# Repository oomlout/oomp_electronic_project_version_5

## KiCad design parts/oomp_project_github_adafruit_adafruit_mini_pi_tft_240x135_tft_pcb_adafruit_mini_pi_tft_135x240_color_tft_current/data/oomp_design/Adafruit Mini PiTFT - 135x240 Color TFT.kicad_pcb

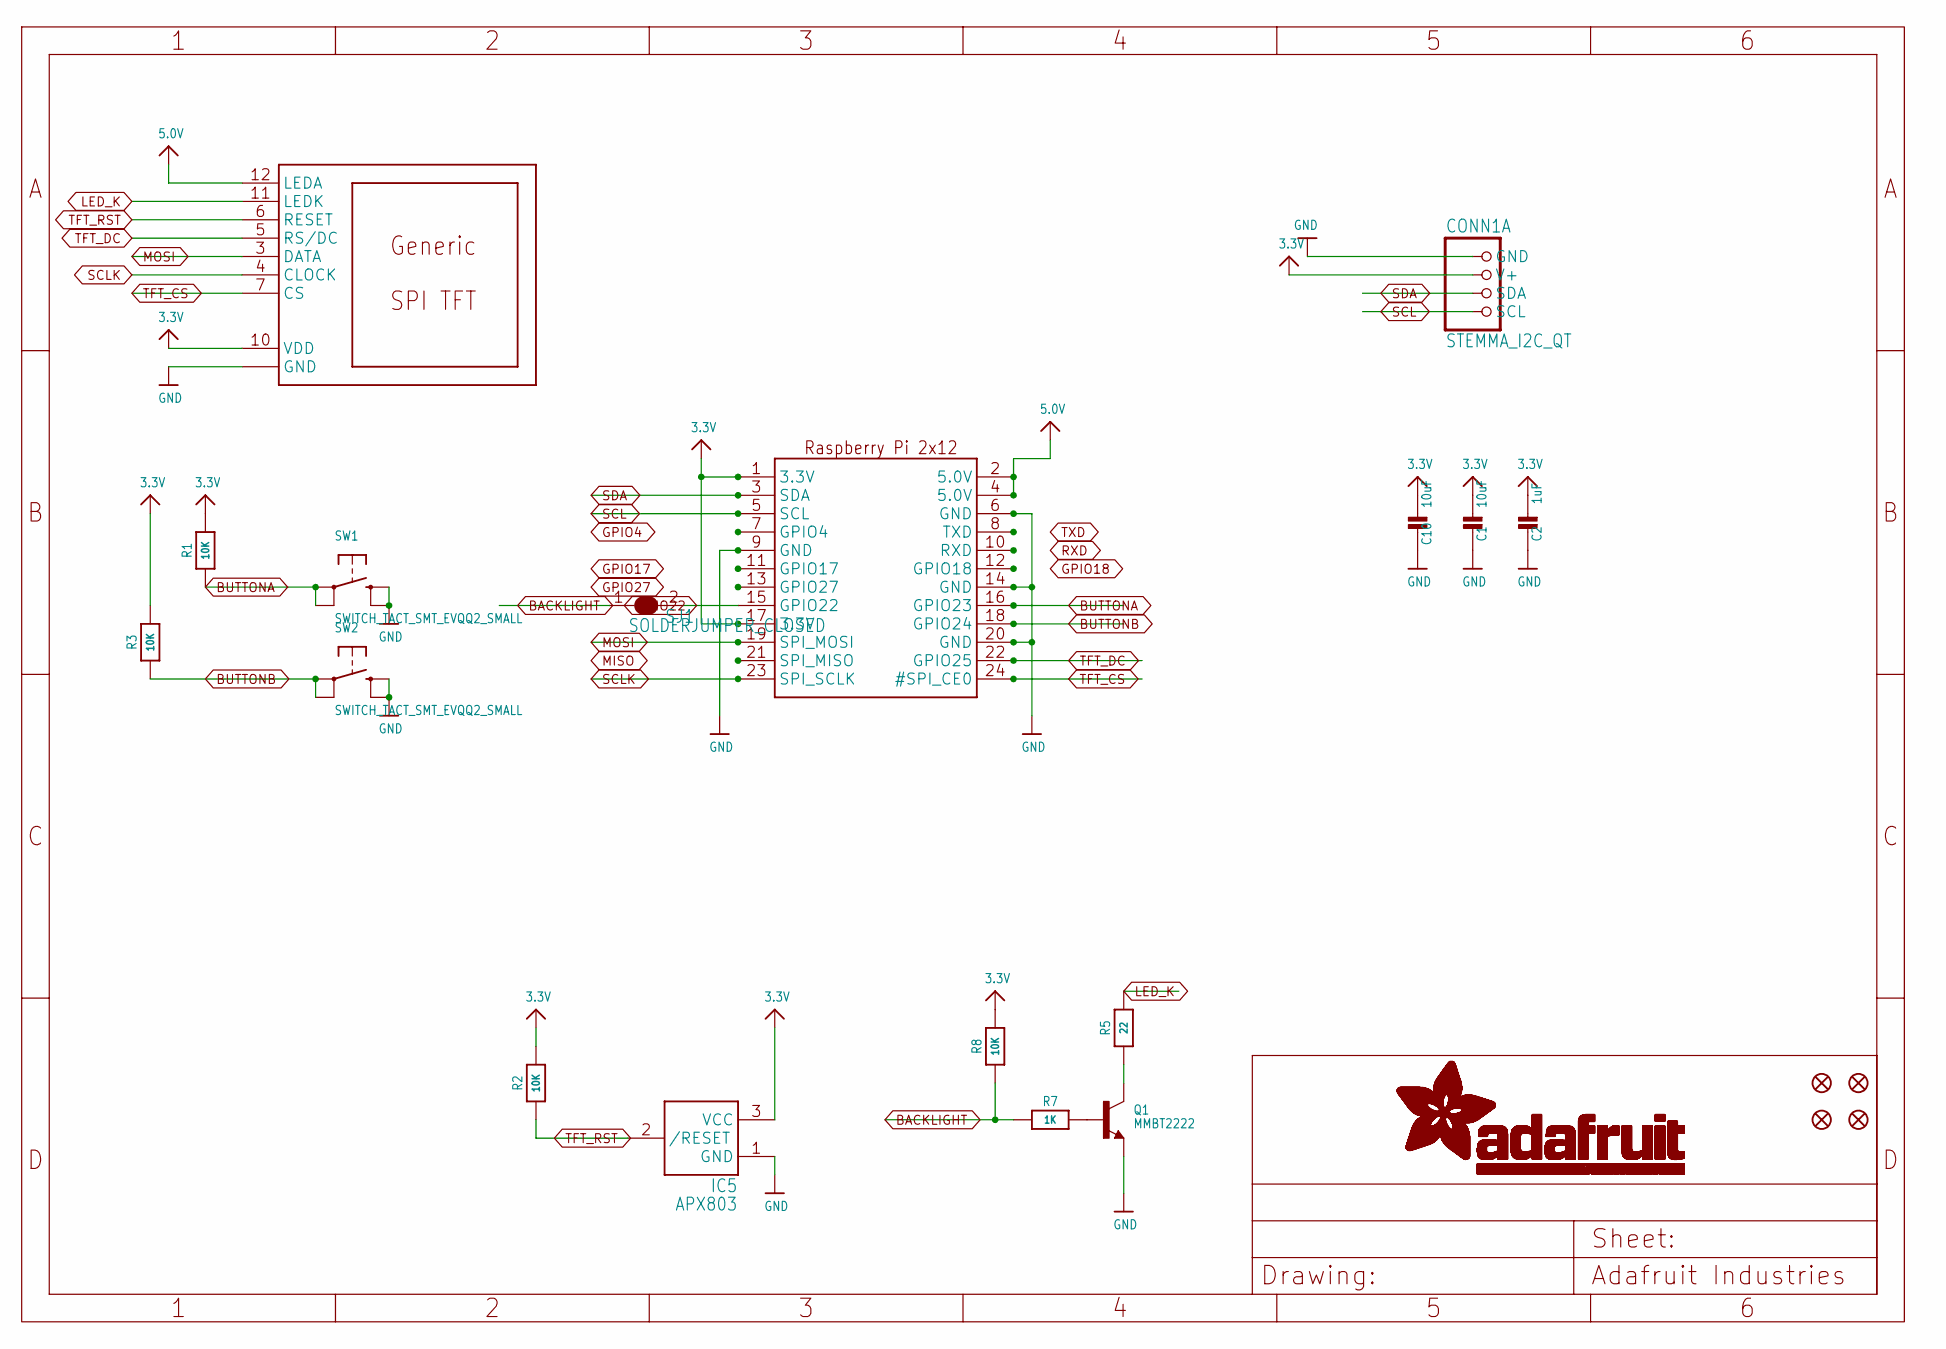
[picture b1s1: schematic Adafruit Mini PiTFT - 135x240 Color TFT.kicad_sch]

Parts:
C1, C10: 10uF; 0805-NO
C2: 1uF; 0603-NO
CONN1: STEMMA_I2C_QT; JST_SH4
DISP1: DISP_LCD_GENERIC_SPI_1.14IN_13P; TFT_1.14IN_240X135_WRAPAROUND
FID1, FID2, FID3, FID4: FIDUCIAL_1MM
IC5: APX803; SOT23
Q1: MMBT2222; SOT23-WIDE
R1, R2, R3, R8: 10K; 0603-NO
R5: 22; 0603-NO
R7: 1K; 0603-NO
RASPI1: RASPBERRYPI_2X12_THMSMT
SJ1: SOLDERJUMPER_CLOSED; SOLDERJUMPER_CLOSEDWIRE
SW1, SW2: SWITCH_TACT_SMT_EVQQ2_SMALL; EVQ-Q2_SMALLER

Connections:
3.3V: C1.2, C2.2, C10.2, CONN1.2 (V+), DISP1.10 (VDD), IC5.3 (VCC), R1.2, R2.2, R3.2, R8.2, RASPI1.1 (3.3V), RASPI1.17 (3.3V)
5.0V: DISP1.12 (LEDA), RASPI1.2 (5.0V), RASPI1.4 (5.0V)
BACKLIGHT: R7.1, R8.1, SJ1.1
BUTTONA: R1.1, RASPI1.16 (GPIO23), SW1.A, SW1.A' (P1)
BUTTONB: R3.1, RASPI1.18 (GPIO24), SW2.A, SW2.A' (P1)
GND: C1.1, C2.1, C10.1, CONN1.1 (GND), DISP1.8 (GND), DISP1.13 (GND), IC5.1 (GND), Q1.2 (E), RASPI1.6 (GND), RASPI1.9 (GND), RASPI1.14 (GND), RASPI1.20 (GND), SW1.B (S), SW1.B' (S1), SW2.B (S), SW2.B' (S1)
GPIO4: RASPI1.7 (GPIO4)
GPIO17: RASPI1.11 (GPIO17)
GPIO18: RASPI1.12 (GPIO18)
GPIO22: RASPI1.15 (GPIO22), SJ1.2
GPIO27: RASPI1.13 (GPIO27)
LED_K: DISP1.11 (LEDK), R5.2
MISO: RASPI1.21 (SPI_MISO)
MOSI: DISP1.3 (DATA), RASPI1.19 (SPI_MOSI)
unnamed: Q1.1 (B), R7.2
unnamed: Q1.3 (C), R5.1
RXD: RASPI1.10 (RXD)
SCL: CONN1.4 (SCL), RASPI1.5 (SCL)
SCLK: DISP1.4 (CLOCK), RASPI1.23 (SPI_SCLK)
SDA: CONN1.3 (SDA), RASPI1.3 (SDA)
TFT_CS: DISP1.7 (CS), RASPI1.24 (#SPI_CE0)
TFT_DC: DISP1.5 (RS/DC), RASPI1.22 (GPIO25)
TFT_RST: DISP1.6 (RESET), IC5.2 (/RESET), R2.1
TXD: RASPI1.8 (TXD)

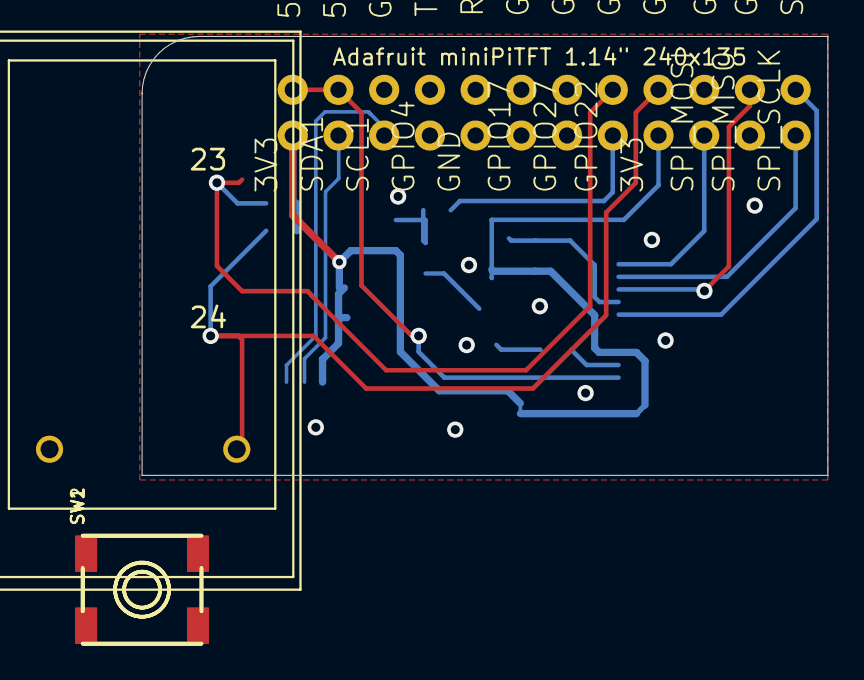
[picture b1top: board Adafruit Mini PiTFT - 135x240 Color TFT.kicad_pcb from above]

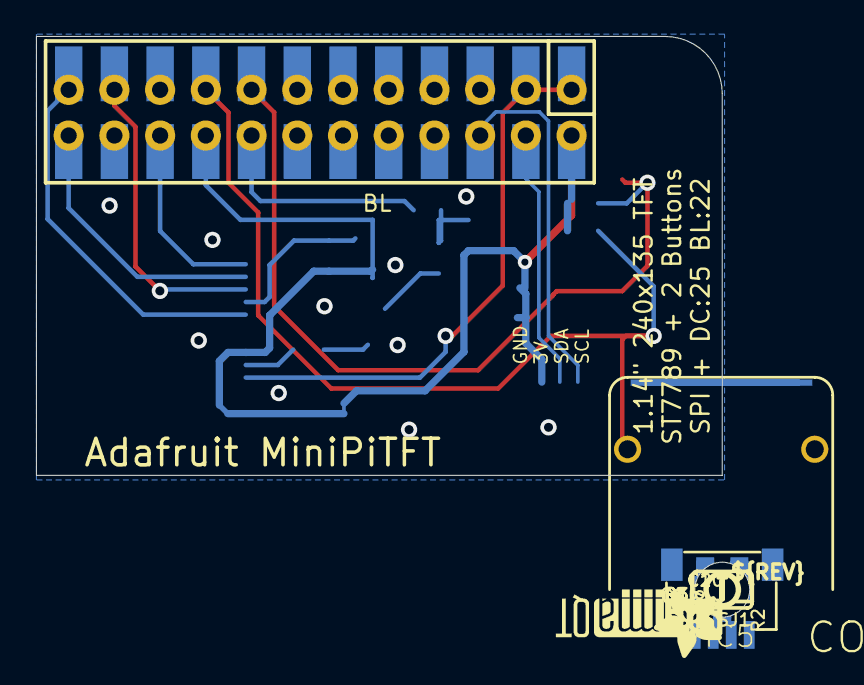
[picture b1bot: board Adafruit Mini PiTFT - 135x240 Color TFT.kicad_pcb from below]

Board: 2 copper layers, 38.1 x 24.4 mm, 25 parts (18 on the bottom side), 17 nets.

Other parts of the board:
U$4: MICROSD; ADAFRUIT_3.5MM
U$6: PCBFEAT-REV-040
U$15: STEMMAQT
UNK_HOLE_0: dummyfp0

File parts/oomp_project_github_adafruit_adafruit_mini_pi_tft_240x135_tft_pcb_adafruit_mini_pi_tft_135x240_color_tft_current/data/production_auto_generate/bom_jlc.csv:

Comment,Designator,Footprint,LCSC Part #
,"SW1,SW2",Adafruit Mini PiTFT - 135x240 Color TFT-import-fps:EVQ-Q2_SMALLER,
,U$6,Adafruit Mini PiTFT - 135x240 Color TFT-import-fps:PCBFEAT-REV-040,
,U$15,Adafruit Mini PiTFT - 135x240 Color TFT-import-fps:STEMMAQT,
10K,"R1,R2,R3,R8",Adafruit Mini PiTFT - 135x240 Color TFT-import-fps:0603-NO,C98220
10uF,"C1,C10",Adafruit Mini PiTFT - 135x240 Color TFT-import-fps:0805-NO,
1K,R7,Adafruit Mini PiTFT - 135x240 Color TFT-import-fps:0603-NO,C2907002
1uF,C2,Adafruit Mini PiTFT - 135x240 Color TFT-import-fps:0603-NO,C5673
22,R5,Adafruit Mini PiTFT - 135x240 Color TFT-import-fps:0603-NO,C23345
APX803,IC5,Adafruit Mini PiTFT - 135x240 Color TFT-import-fps:SOT23,
DISP_LCD_GENERIC_SPI_1.14IN_13P,DISP1,Adafruit Mini PiTFT - 135x240 Color TFT-import-fps:TFT_1.14IN_240X135_WRAPAROUND,
MICROSD,U$4,Adafruit Mini PiTFT - 135x240 Color TFT-import-fps:ADAFRUIT_3.5MM,
MMBT2222,Q1,Adafruit Mini PiTFT - 135x240 Color TFT-import-fps:SOT23-WIDE,
RASPBERRYPI_2X12_THMSMT,RASPI1,Adafruit Mini PiTFT - 135x240 Color TFT-import-fps:RASPBERRYPI_2X12_THMSMT,
STEMMA_I2C_QT,CONN1,Adafruit Mini PiTFT - 135x240 Color TFT-import-fps:JST_SH4,C160404

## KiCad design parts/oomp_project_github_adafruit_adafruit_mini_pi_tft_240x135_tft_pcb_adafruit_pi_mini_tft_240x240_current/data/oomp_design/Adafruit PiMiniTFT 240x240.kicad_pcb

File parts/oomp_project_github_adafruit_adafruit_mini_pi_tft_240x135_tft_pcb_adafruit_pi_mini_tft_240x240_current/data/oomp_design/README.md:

# OOMP KiCad design copy

Open `Adafruit PiMiniTFT 240x240.kicad_pro` (or the `.kicad_pcb` / `.kicad_sch`) in KiCad. Local OOMP libraries are under `libraries/`. Original inputs are preserved in [../original/](../original/).

Only verified unchanged installed KiCad defaults were renamed. Modified, custom, unmatched and unavailable items remain unchanged. Soldering variants are never swapped during conversion. Existing pad coordinates, nets and UUIDs are preserved.

See [conversion_report.yaml](conversion_report.yaml) for every conversion and skip. Copy this directory before editing; regeneration refuses to overwrite edited design files.

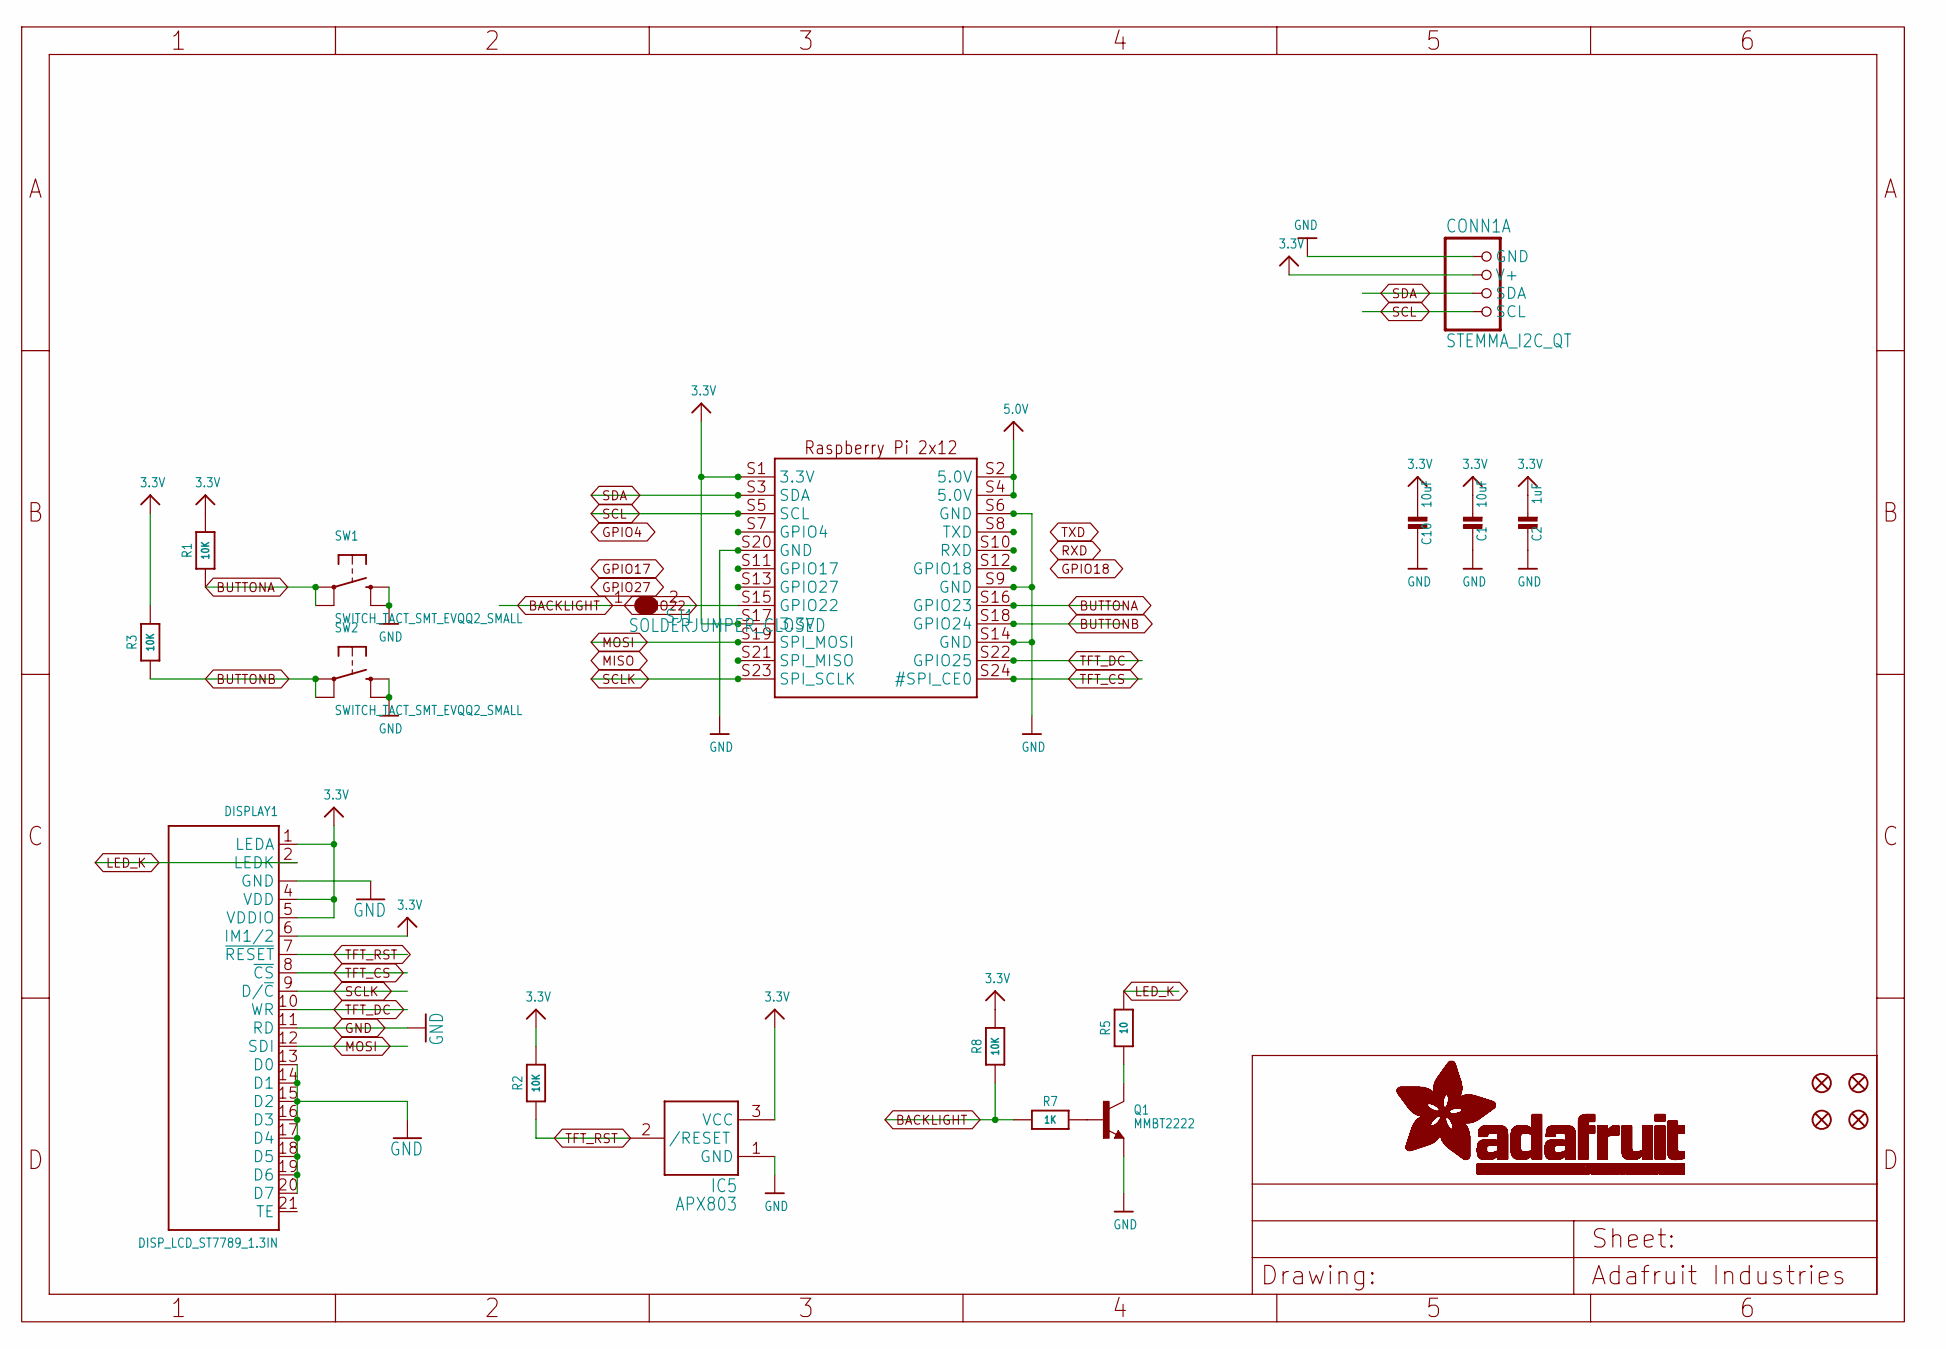
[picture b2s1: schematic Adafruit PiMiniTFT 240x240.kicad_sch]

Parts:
C1, C10: 10uF; 0805-NO
C2: 1uF; 0603-NO
CONN1: STEMMA_I2C_QT; JST_SH4
DISPLAY1: DISP_LCD_ST7789_1.3IN; TFT_1.3IN_240X240_24P
FID1, FID2, FID3, FID4: FIDUCIAL_1MM
IC5: APX803; SOT23
Q1: MMBT2222; SOT23-WIDE
R1, R2, R3, R8: 10K; 0603-NO
R5: 10; 0603-NO
R7: 1K; 0603-NO
RASPI1: RASPBERRYPI_2X12_SMT
SJ1: SOLDERJUMPER_CLOSED; SOLDERJUMPER_CLOSEDWIRE
SW1, SW2: SWITCH_TACT_SMT_EVQQ2_SMALL; EVQ-Q2_SMALLER

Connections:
3.3V: C1.2, C2.2, C10.2, CONN1.2 (V+), DISPLAY1.1 (LEDA), DISPLAY1.4 (VDD), DISPLAY1.5 (VDDIO), DISPLAY1.6 (IM1/2), IC5.3 (VCC), R1.2, R2.2, R3.2, R8.2, RASPI1.S1 (3.3V), RASPI1.S17 (3.3V)
5.0V: RASPI1.S2 (5.0V), RASPI1.S4 (5.0V)
BACKLIGHT: R7.1, R8.1, SJ1.1
BUTTONA: R1.1, RASPI1.S16 (GPIO23), SW1.A, SW1.A' (P1)
BUTTONB: R3.1, RASPI1.S18 (GPIO24), SW2.A, SW2.A' (P1)
GND: C1.1, C2.1, C10.1, CONN1.1 (GND), DISPLAY1.3 (GND), DISPLAY1.11 (RD), DISPLAY1.13 (D0), DISPLAY1.14 (D1), DISPLAY1.15 (D2), DISPLAY1.16 (D3), DISPLAY1.17 (D4), DISPLAY1.18 (D5), DISPLAY1.19 (D6), DISPLAY1.20 (D7), DISPLAY1.23 (GND), DISPLAY1.24 (GND), IC5.1 (GND), Q1.2 (E), RASPI1.S6 (GND), RASPI1.S9 (GND), RASPI1.S14 (GND), RASPI1.S20 (GND), SW1.B (S), SW1.B' (S1), SW2.B (S), SW2.B' (S1)
GPIO4: RASPI1.S7 (GPIO4)
GPIO17: RASPI1.S11 (GPIO17)
GPIO18: RASPI1.S12 (GPIO18)
GPIO22: RASPI1.S15 (GPIO22), SJ1.2
GPIO27: RASPI1.S13 (GPIO27)
LED_K: DISPLAY1.2 (LEDK), R5.2
MISO: RASPI1.S21 (SPI_MISO)
MOSI: DISPLAY1.12 (SDI), RASPI1.S19 (SPI_MOSI)
unnamed: Q1.1 (B), R7.2
unnamed: Q1.3 (C), R5.1
RXD: RASPI1.S10 (RXD)
SCL: CONN1.4 (SCL), RASPI1.S5 (SCL)
SCLK: DISPLAY1.9 (D/~C), RASPI1.S23 (SPI_SCLK)
SDA: CONN1.3 (SDA), RASPI1.S3 (SDA)
TFT_CS: DISPLAY1.8 (~CS), RASPI1.S24 (#SPI_CE0)
TFT_DC: DISPLAY1.10 (WR), RASPI1.S22 (GPIO25)
TFT_RST: DISPLAY1.7 (~RESET), IC5.2 (/RESET), R2.1
TXD: RASPI1.S8 (TXD)

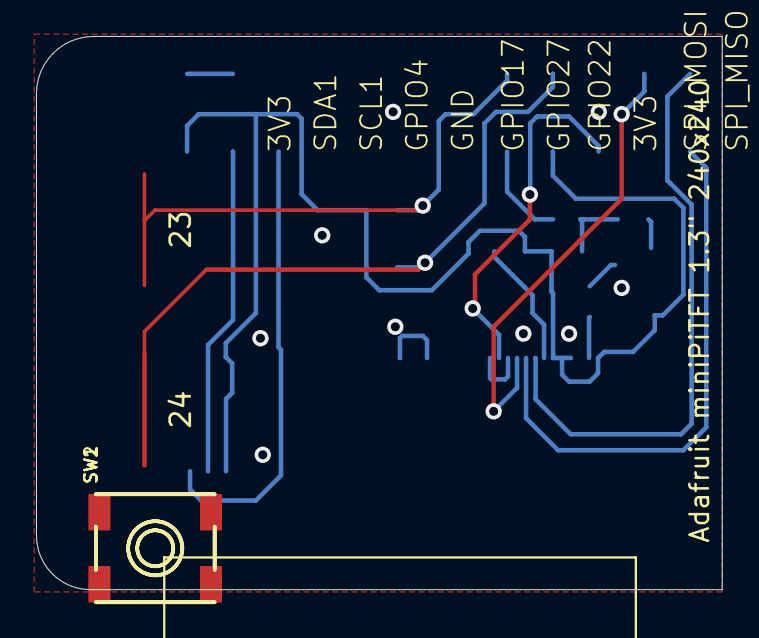
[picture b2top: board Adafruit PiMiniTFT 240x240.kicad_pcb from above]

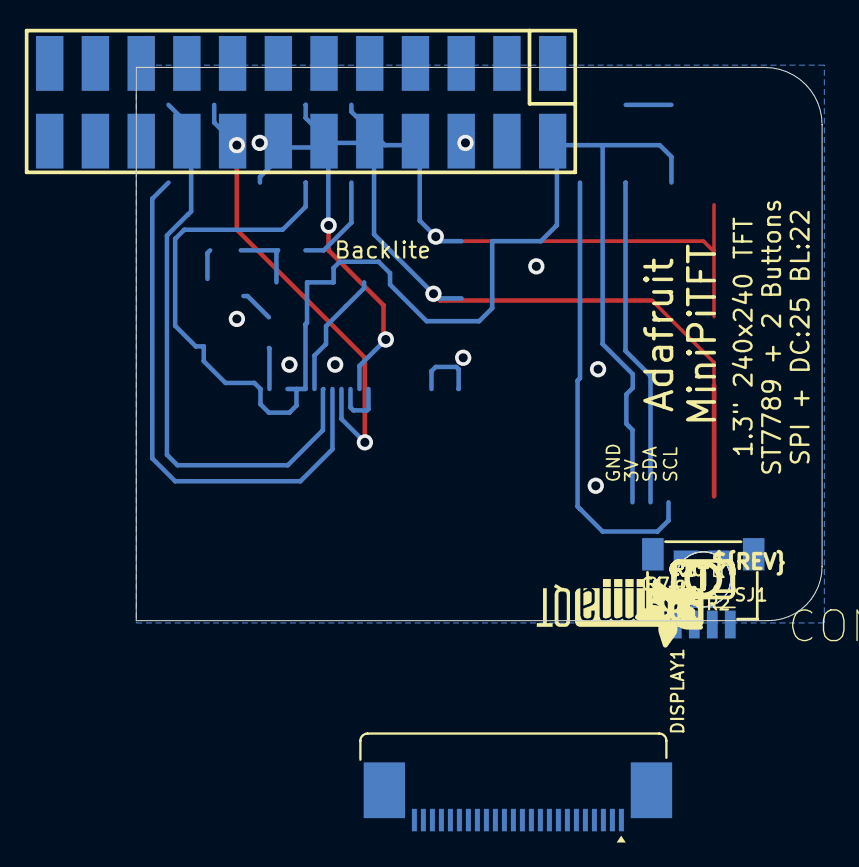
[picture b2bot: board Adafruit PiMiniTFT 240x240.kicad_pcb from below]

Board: 2 copper layers, 38.1 x 30.7 mm, 26 parts (19 on the bottom side), 17 nets.

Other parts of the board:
U$4: MICROSD; ADAFRUIT_3.5MM
U$6: PCBFEAT-REV-040
U$15: STEMMAQT
UNK_HOLE_0: dummyfp0
UNK_HOLE_1: dummyfp1

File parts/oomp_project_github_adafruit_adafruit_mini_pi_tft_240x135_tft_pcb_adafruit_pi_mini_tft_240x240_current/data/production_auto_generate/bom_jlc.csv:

Comment,Designator,Footprint,LCSC Part #
,"SW1,SW2",Adafruit PiMiniTFT 240x240-import-fps:EVQ-Q2_SMALLER,
,U$6,Adafruit PiMiniTFT 240x240-import-fps:PCBFEAT-REV-040,
,U$15,Adafruit PiMiniTFT 240x240-import-fps:STEMMAQT,
10,R5,Adafruit PiMiniTFT 240x240-import-fps:0603-NO,C22859
10K,"R1,R2,R3,R8",Adafruit PiMiniTFT 240x240-import-fps:0603-NO,C98220
10uF,"C1,C10",Adafruit PiMiniTFT 240x240-import-fps:0805-NO,
1K,R7,Adafruit PiMiniTFT 240x240-import-fps:0603-NO,C2907002
1uF,C2,Adafruit PiMiniTFT 240x240-import-fps:0603-NO,C5673
APX803,IC5,Adafruit PiMiniTFT 240x240-import-fps:SOT23,
DISP_LCD_ST7789_1.3IN,DISPLAY1,Adafruit PiMiniTFT 240x240-import-fps:TFT_1.3IN_240X240_24P,
MICROSD,U$4,Adafruit PiMiniTFT 240x240-import-fps:ADAFRUIT_3.5MM,
MMBT2222,Q1,Adafruit PiMiniTFT 240x240-import-fps:SOT23-WIDE,
RASPBERRYPI_2X12_SMT,RASPI1,Adafruit PiMiniTFT 240x240-import-fps:RASPBERRYPI_2X12_SMT,
STEMMA_I2C_QT,CONN1,Adafruit PiMiniTFT 240x240-import-fps:JST_SH4,C160404

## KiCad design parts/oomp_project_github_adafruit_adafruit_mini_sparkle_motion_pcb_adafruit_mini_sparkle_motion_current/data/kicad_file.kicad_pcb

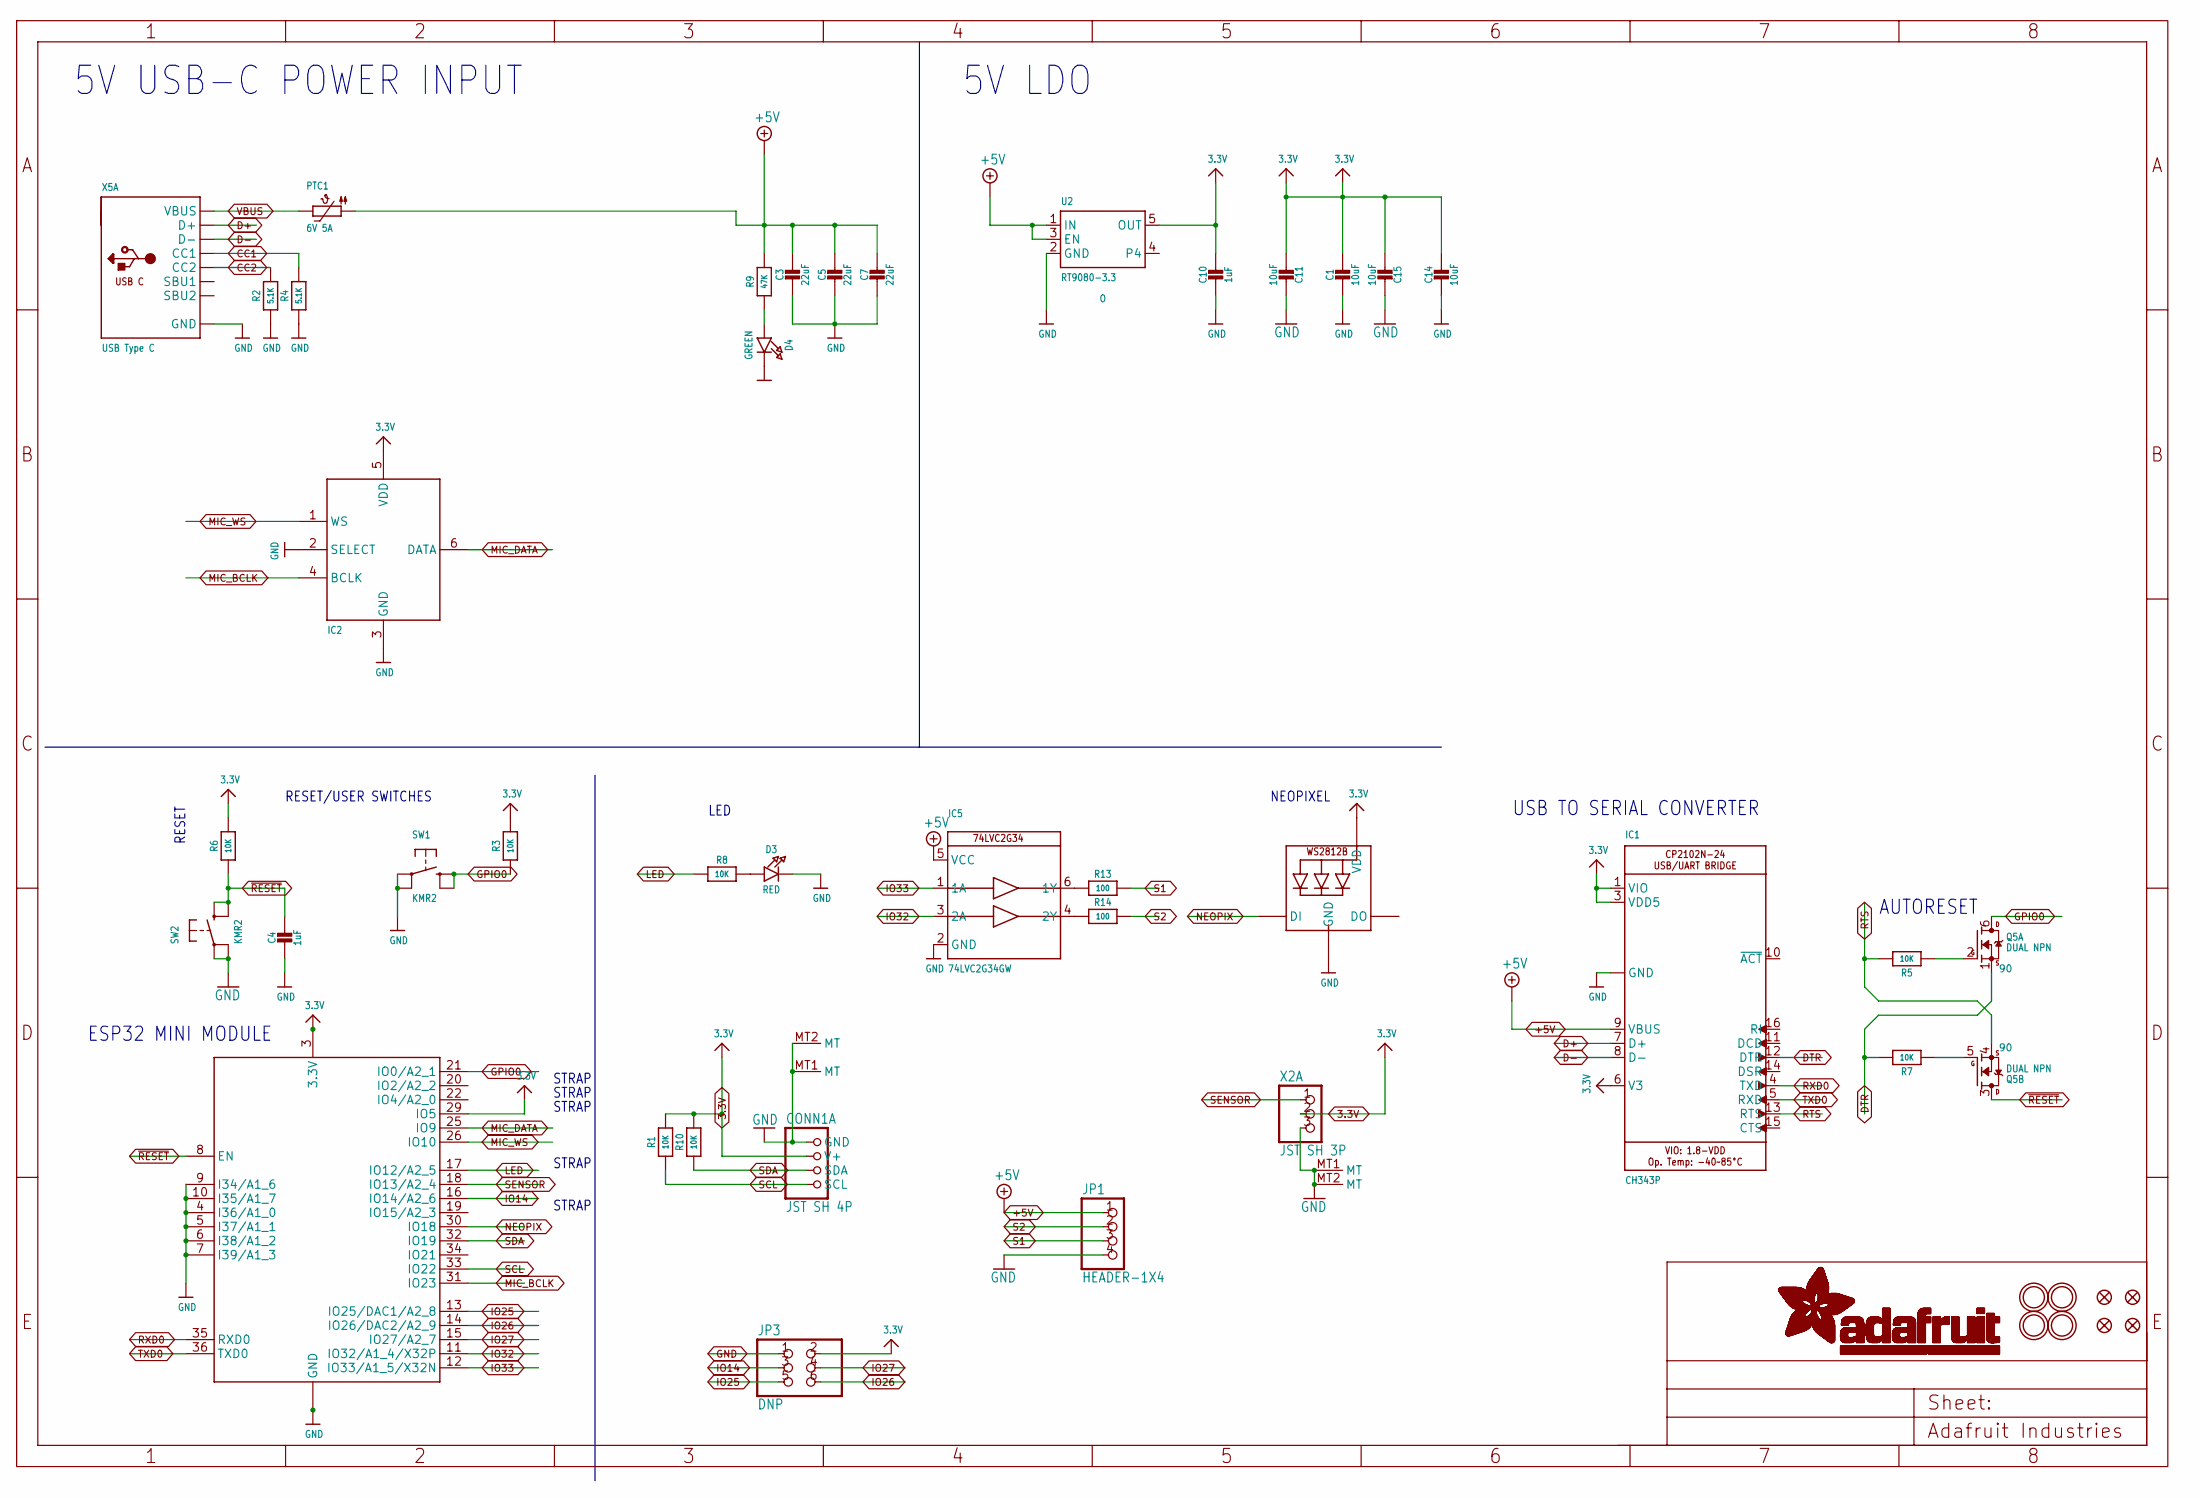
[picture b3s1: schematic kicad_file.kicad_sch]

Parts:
C1, C11, C14, C15: 10uF; 0805-NO
C3, C5, C7: 22uF; 0805-NO
C4, C10: 1uF; _0402NO
CONN1: JST SH 4P; JST_SH4; LCSC C2845363
D3: RED; CHIPLED_0603_NOOUTLINE
D4: GREEN; CHIPLED_0603_NOOUTLINE
IC1: CH343P; QFN16_3MM
IC2: ICS-43434; SPH0645LM4H
IC5: 74LVC2G34GW; SC70-6L
JP1: HEADER-1X4; 1X04_OVAL
JP3: DNP; 2X03_ROUND_70MIL
LED1: WS2812B_SK6805_1515; SK6805_1515; LCSC C2890035
PTC1: 6V 5A; PTC1210
Q5: DUAL NPN; SOT363; JLC_ROTATION 90
R1, R3, R5, R6, R7, R8, R10: 10K; _0402NO
R2, R4: 5.1K; _0402NO
R9: 47K; _0402NO
R13, R14: 100; _0402NO
SW1, SW2: KMR2; BTN_RKB2_4.6X2.8
U2: RT9080-3.3; SOT23-5; JLC_ROTATION 0
U$14, U$20, U$28, U$31: MOUNTINGHOLE2.5; MOUNTINGHOLE_2.5_PLATED
U$23, U$25, U$34, U$35: FIDUCIAL_0.5MM
X2: JST SH 3P; JST_SH3
X4: ESP32-MINI-1
X5: USB Type C; USB_C_CUSB31-CFM2AX-01-X; LCSC C165948

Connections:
3.3V: C1.1, C10.1, C11.1, C14.1, C15.1, CONN1.2 (V+), IC1.1 (VIO), IC1.3 (VDD5), IC1.6 (V3), IC2.5 (VDD), JP3.2, LED1.2 (VDD), R1.2, R3.2, R6.2, R10.2, U2.5 (OUT), X2.2, X4.3 (3.3V), X4.29 (IO5)
+5V: C3.1, C5.1, C7.1, IC1.9 (VBUS), IC5.5 (VCC), JP1.1, PTC1.P$1 (1), R9.2, U2.1 (IN), U2.3 (EN)
CC1: R4.2, X5.A5 (CC1)
CC2: R2.2, X5.B5 (CC2)
D+: IC1.7 (D+), X5.A6 (D+), X5.B6 (D+)
D-: IC1.8 (D-), X5.A7 (D-), X5.B7 (D-)
DTR: IC1.12 (DTR), Q5.1 (S), R7.2
GND: C1.2, C3.2, C4.2, C5.2, C7.2, C10.2, C11.2, C14.2, C15.2, CONN1.1 (GND), CONN1.MT1 (MT), CONN1.MT2 (MT), D3.C, D4.C, IC1.2 (GND), IC1.THERMAL (GND), IC2.2 (SELECT), IC2.3 (GND), IC5.2 (GND), JP1.4, JP3.1, LED1.4 (GND), R2.1, R4.1, SW1.A, SW1.A' (P1), SW2.A, SW2.A' (P1), U2.2 (GND), X2.3, X2.MT1 (MT), X2.MT2 (MT), X4.1 (GND), X4.2 (GND), X4.4 (I36/A1_0), X4.5 (I37/A1_1), X4.6 (I38/A1_2), X4.7 (I39/A1_3), X4.9 (I34/A1_6), X4.10 (I35/A1_7), X4.27 (GND), X4.38 (GND), X4.39 (GND), X4.40 (GND), X4.41 (GND), X4.42 (GND), X4.43 (GND), X4.44 (GND), X4.45 (GND), X4.46 (GND), X4.47 (GND), X4.48 (GND), X4.49 (GND), X4.50 (GND), X4.51 (GND), X4.52 (GND), X4.53 (GND), X4.54 (GND), X4.55 (GND), X4.56 (GND), X4.57 (GND), X4.58 (GND), X4.59 (GND), X4.60 (GND), X4.61 (GND), X4.62 (GND), X4.63 (GND), X5.A1B12 (GND), X5.B1A12 (GND)
GPIO0: Q5.6 (D), R3.1, SW1.B (S), SW1.B' (S1), X4.21 (IO0/A2_1)
IO14: JP3.3, X4.16 (IO14/A2_6)
IO25: JP3.5, X4.13 (IO25/DAC1/A2_8)
IO26: JP3.6, X4.14 (IO26/DAC2/A2_9)
IO27: JP3.4, X4.15 (IO27/A2_7)
IO32: IC5.3 (2A), X4.11 (IO32/A1_4/X32P)
IO33: IC5.1 (1A), X4.12 (IO33/A1_5/X32N)
LED: R8.1, X4.17 (IO12/A2_5)
MIC_BCLK: IC2.4 (BCLK), X4.31 (IO23)
MIC_DATA: IC2.6 (DATA), X4.25 (IO9)
MIC_WS: IC2.1 (WS), X4.26 (IO10)
unnamed: D3.A, R8.2
unnamed: Q5.5 (G), R7.1
unnamed: Q5.2 (G), R5.1
unnamed: IC5.6 (1Y), R13.1
unnamed: IC5.4 (2Y), R14.1
unnamed: D4.A, R9.1
NEOPIX: LED1.1 (DI), X4.30 (IO18)
RTS: IC1.13 (RTS), Q5.4 (S), R5.2
RXD0: IC1.4 (TXD), X4.35 (RXD0)
S1: JP1.3, R13.2
S2: JP1.2, R14.2
SCL: CONN1.4 (SCL), R1.1, X4.33 (IO22)
SDA: CONN1.3 (SDA), R10.1, X4.32 (IO19)
SENSOR: X2.1, X4.18 (IO13/A2_4)
TXD0: IC1.5 (RXD), X4.36 (TXD0)
VBUS: PTC1.P$2 (2), X5.A4B9 (VBUS), X5.B4A9 (VBUS)
~RESET: C4.1, Q5.3 (D), R6.1, SW2.B (S), SW2.B' (S1), X4.8 (EN)

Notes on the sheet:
STRAP
AUTORESET
USB TO SERIAL CONVERTER
NEOPIXEL
ESP32 MINI MODULE
RESET/USER SWITCHES
5V USB-C POWER INPUT
LED
RESET
5V LDO

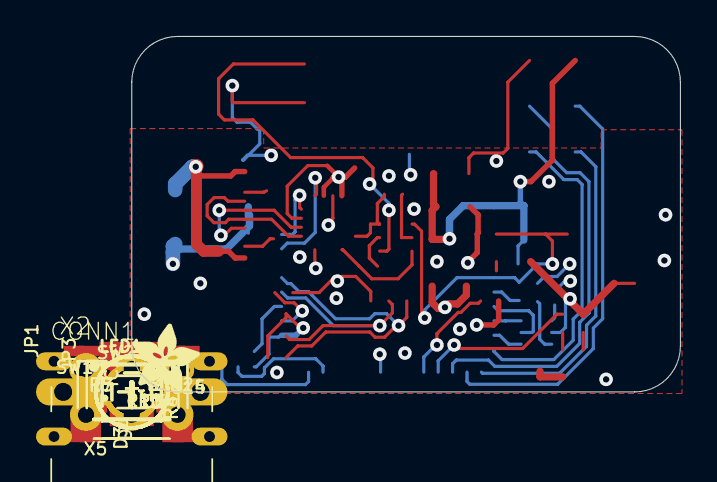
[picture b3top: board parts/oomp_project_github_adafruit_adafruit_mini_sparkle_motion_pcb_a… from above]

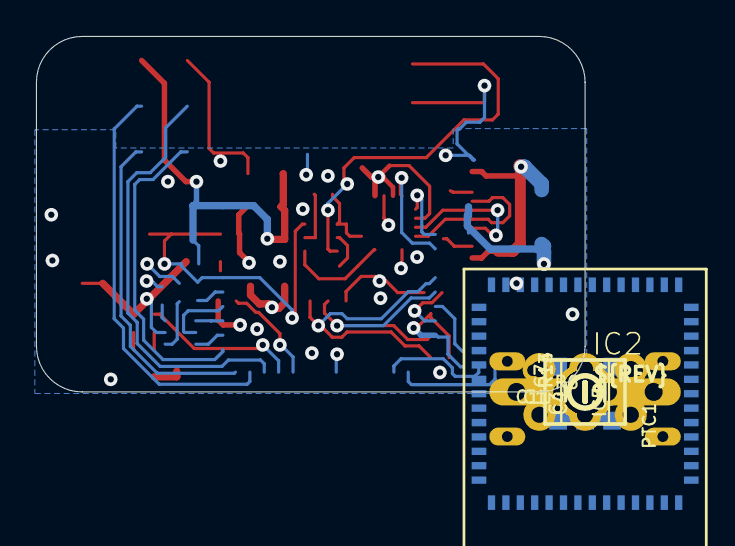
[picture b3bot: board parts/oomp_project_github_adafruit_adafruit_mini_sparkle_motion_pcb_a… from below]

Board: 4 copper layers, 30.5 x 19.7 mm, 68 parts (22 on the bottom side), 36 nets.

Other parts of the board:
PLABEL0: PLABEL0
PLABEL1: PLABEL1
PLABEL2: PLABEL2
PLABEL3: PLABEL3
PLABEL4: PLABEL4
PLABEL5: PLABEL5
PLABEL6: PLABEL6
PLABEL7: PLABEL7
PLABEL8: PLABEL8
PLABEL9: PLABEL9
PLABEL10: PLABEL10
PLABEL11: PLABEL11
PLABEL15: PLABEL15
PLABEL16: PLABEL16
PLABEL17: PLABEL17
PLABEL18: PLABEL18
PLABEL20: PLABEL20
PLABEL21: PLABEL21
PLABEL22: PLABEL22
PLABEL23: PLABEL23
U$27: ADAFRUIT_3.5MM
U$29: PCBFEAT-REV-040

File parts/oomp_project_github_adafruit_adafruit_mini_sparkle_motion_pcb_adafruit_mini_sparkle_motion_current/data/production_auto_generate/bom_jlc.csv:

Comment,Designator,Footprint,LCSC Part #
,JP1,Adafruit Mini Sparkle Motion-import-fps:1X04_OVAL,C42431795
,U$27,Adafruit Mini Sparkle Motion-import-fps:ADAFRUIT_3.5MM,
,U$29,Adafruit Mini Sparkle Motion-import-fps:PCBFEAT-REV-040,
,PLABEL0,Adafruit Mini Sparkle Motion-import-fps:PLABEL0,
,PLABEL1,Adafruit Mini Sparkle Motion-import-fps:PLABEL1,
,PLABEL10,Adafruit Mini Sparkle Motion-import-fps:PLABEL10,
,PLABEL11,Adafruit Mini Sparkle Motion-import-fps:PLABEL11,
,PLABEL15,Adafruit Mini Sparkle Motion-import-fps:PLABEL15,
,PLABEL16,Adafruit Mini Sparkle Motion-import-fps:PLABEL16,
,PLABEL17,Adafruit Mini Sparkle Motion-import-fps:PLABEL17,
,PLABEL18,Adafruit Mini Sparkle Motion-import-fps:PLABEL18,
,PLABEL2,Adafruit Mini Sparkle Motion-import-fps:PLABEL2,
,PLABEL20,Adafruit Mini Sparkle Motion-import-fps:PLABEL20,
,PLABEL21,Adafruit Mini Sparkle Motion-import-fps:PLABEL21,
,PLABEL22,Adafruit Mini Sparkle Motion-import-fps:PLABEL22,
,PLABEL23,Adafruit Mini Sparkle Motion-import-fps:PLABEL23,
,PLABEL3,Adafruit Mini Sparkle Motion-import-fps:PLABEL3,
,PLABEL4,Adafruit Mini Sparkle Motion-import-fps:PLABEL4,
,PLABEL5,Adafruit Mini Sparkle Motion-import-fps:PLABEL5,
,PLABEL6,Adafruit Mini Sparkle Motion-import-fps:PLABEL6,
,PLABEL7,Adafruit Mini Sparkle Motion-import-fps:PLABEL7,
,PLABEL8,Adafruit Mini Sparkle Motion-import-fps:PLABEL8,
,PLABEL9,Adafruit Mini Sparkle Motion-import-fps:PLABEL9,
100,"R13,R14",Adafruit Mini Sparkle Motion-import-fps:_0402NO,C2906860
10K,"R1,R3,R5,R6,R7,R8,R10",Adafruit Mini Sparkle Motion-import-fps:_0402NO,C2906861
10uF,"C1,C11,C14,C15",Adafruit Mini Sparkle Motion-import-fps:0805-NO,
1uF,"C4,C10",Adafruit Mini Sparkle Motion-import-fps:_0402NO,C2887021
22uF,"C3,C5,C7",Adafruit Mini Sparkle Motion-import-fps:0805-NO,
47K,R9,Adafruit Mini Sparkle Motion-import-fps:_0402NO,C25792
5.1K,"R2,R4",Adafruit Mini Sparkle Motion-import-fps:_0402NO,C25905
6V 5A,PTC1,Adafruit Mini Sparkle Motion-import-fps:PTC1210,
74LVC2G34GW,IC5,Adafruit Mini Sparkle Motion-import-fps:SC70-6L,
CH343P,IC1,Adafruit Mini Sparkle Motion-import-fps:QFN16_3MM,
DNP,JP3,Adafruit Mini Sparkle Motion-import-fps:2X03_ROUND_70MIL,
DUAL NPN,Q5,Adafruit Mini Sparkle Motion-import-fps:SOT363,
ESP32-MINI-1,X4,Adafruit Mini Sparkle Motion-import-fps:ESP32-MINI-1,
FIDUCIAL_0.5MM,"U$23,U$25,U$34,U$35",Adafruit Mini Sparkle Motion-import-fps:FIDUCIAL_0.5MM,
GREEN,D4,Adafruit Mini Sparkle Motion-import-fps:CHIPLED_0603_NOOUTLINE,
ICS-43434,IC2,Adafruit Mini Sparkle Motion-import-fps:SPH0645LM4H,
JST SH 3P,X2,Adafruit Mini Sparkle Motion-import-fps:JST_SH3,C265338
JST SH 4P,CONN1,Adafruit Mini Sparkle Motion-import-fps:JST_SH4,C160404
KMR2,"SW1,SW2",Adafruit Mini Sparkle Motion-import-fps:BTN_RKB2_4.6X2.8,
RED,D3,Adafruit Mini Sparkle Motion-import-fps:CHIPLED_0603_NOOUTLINE,
RT9080-3.3,U2,Adafruit Mini Sparkle Motion-import-fps:SOT23-5,
USB Type C,X5,Adafruit Mini Sparkle Motion-import-fps:USB_C_CUSB31-CFM2AX-01-X,
WS2812B_SK6805_1515,LED1,Adafruit Mini Sparkle Motion-import-fps:SK6805_1515,

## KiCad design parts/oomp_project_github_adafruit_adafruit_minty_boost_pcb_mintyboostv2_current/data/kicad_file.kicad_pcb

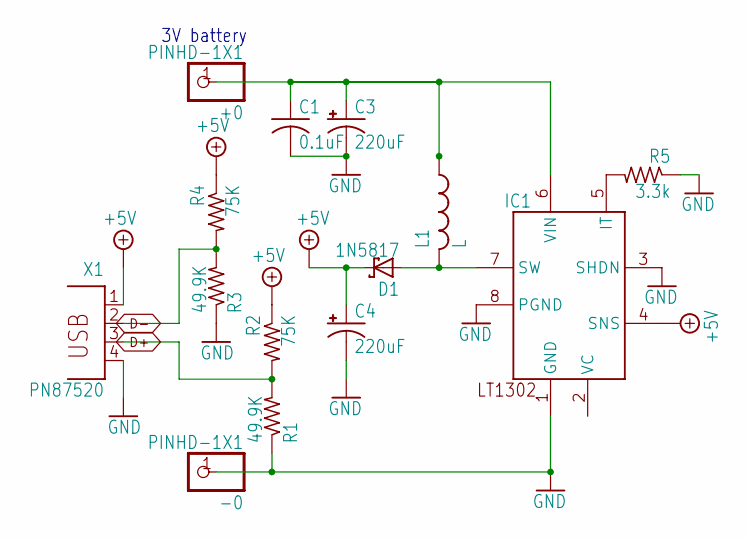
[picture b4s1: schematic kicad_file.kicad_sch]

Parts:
+0: PINHD-1X1; 1X01
-0: PINHD-1X1; 1X01
C1: 0.1uF; C025-025X050
C3, C4: 220uF; E2,5-5
D1: 1N5817; DO41-7
IC1: LT1302; DIL08
L1: L; 6000
R1, R3: 49.9K; 0204_5
R2, R4: 75K; 0204_5
R5: 3.3k; 0204_5
X1: PN87520

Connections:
+5V: C4.+, D1.C, IC1.4 (SNS), R2.1, R4.1, X1.1
BATT+: +0.1, C1.1, C3.+, IC1.6 (VIN), L1.1
D+: R1.2, R2.2, X1.3
D-: R3.2, R4.2, X1.2
GND: -0.1, C1.2, C3.-, C4.-, IC1.1 (GND), IC1.3 (SHDN), IC1.8 (PGND), R1.1, R3.1, R5.1, X1.4
unnamed: IC1.5 (IT), R5.2
unnamed: D1.A, IC1.7 (SW), L1.2

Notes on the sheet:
3V battery

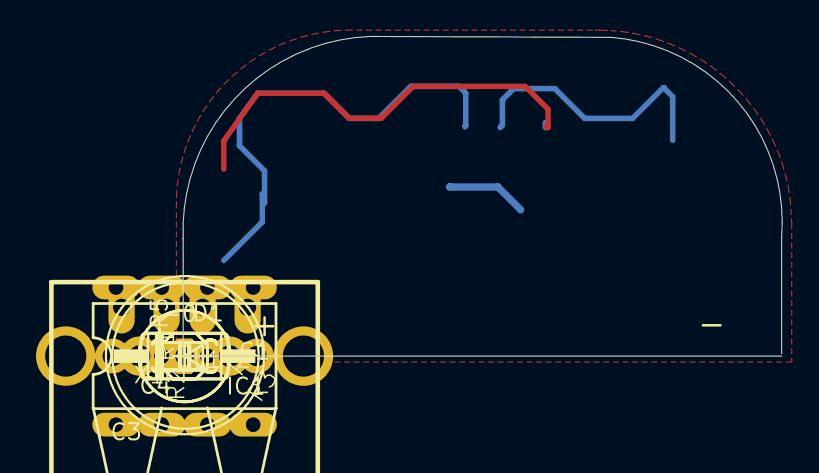
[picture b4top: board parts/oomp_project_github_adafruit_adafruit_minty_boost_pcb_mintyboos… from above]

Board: 16 copper layers, 33.3 x 17.8 mm, 14 parts (0 on the bottom side), 7 nets.

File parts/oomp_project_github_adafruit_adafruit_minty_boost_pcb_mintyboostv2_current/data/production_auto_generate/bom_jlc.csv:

Comment,Designator,Footprint,LCSC Part #
,"+0,-0",mintyboostv2-import-fps:1X01,C7501259
,X1,mintyboostv2-import-fps:PN87520,
0.1uF,C1,mintyboostv2-import-fps:C025-025X050,
1N5817,D1,mintyboostv2-import-fps:DO41-7,
220uF,"C3,C4","mintyboostv2-import-fps:E2,5-5",
3.3k,R5,mintyboostv2-import-fps:0204_5,
49.9K,"R1,R3",mintyboostv2-import-fps:0204_5,
75K,"R2,R4",mintyboostv2-import-fps:0204_5,
L,L1,mintyboostv2-import-fps:6000,
LT1302,IC1,mintyboostv2-import-fps:DIL08,
